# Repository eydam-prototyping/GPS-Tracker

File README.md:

# GPS Tracker Project Documentation

## Project Overview
This project involves developing a GPS tracker using a Raspberry Pi Pico (RP2040) and a SIM7040G module with a built-in GPS. The device will publish its location and cell data to AWS IoT Core every 5 minutes.

## Hardware Components
- **Raspberry Pi Pico (RP2040)**: Main microcontroller.
- **SIM7040G Module**: Provides LTE connectivity and GPS functionality.
- **Battery**: Powers the device.

## Software and Connectivity
- **MicroPython**: Programming language for the Raspberry Pi Pico.
- **AWS IoT Core**: Cloud service for receiving and storing GPS data.

## State Machine Design
### States
1. **Boot State**: System initialization and hardware checks.
2. **Configuration State**: Network and MQTT setup, GPS module initialization.
3. **Idle State**: Low-power mode between data transmissions.
4. **Track State**: Active data retrieval and transmission to AWS.
5. **Error State**: Error detection and handling.

## Error Handling Best Practices
- Clear identification and logging of errors.
- Graceful degradation and automated recovery.
- User notification for critical errors.
- Regular health checks for system components.

## Power Management
Implement power-saving techniques, especially in the Idle State, to extend battery life.

## Future Steps
- Testing and debugging the system.
- Designing a custom PCB integrating all components.
- Optimizing for efficient power usage and network reliability.

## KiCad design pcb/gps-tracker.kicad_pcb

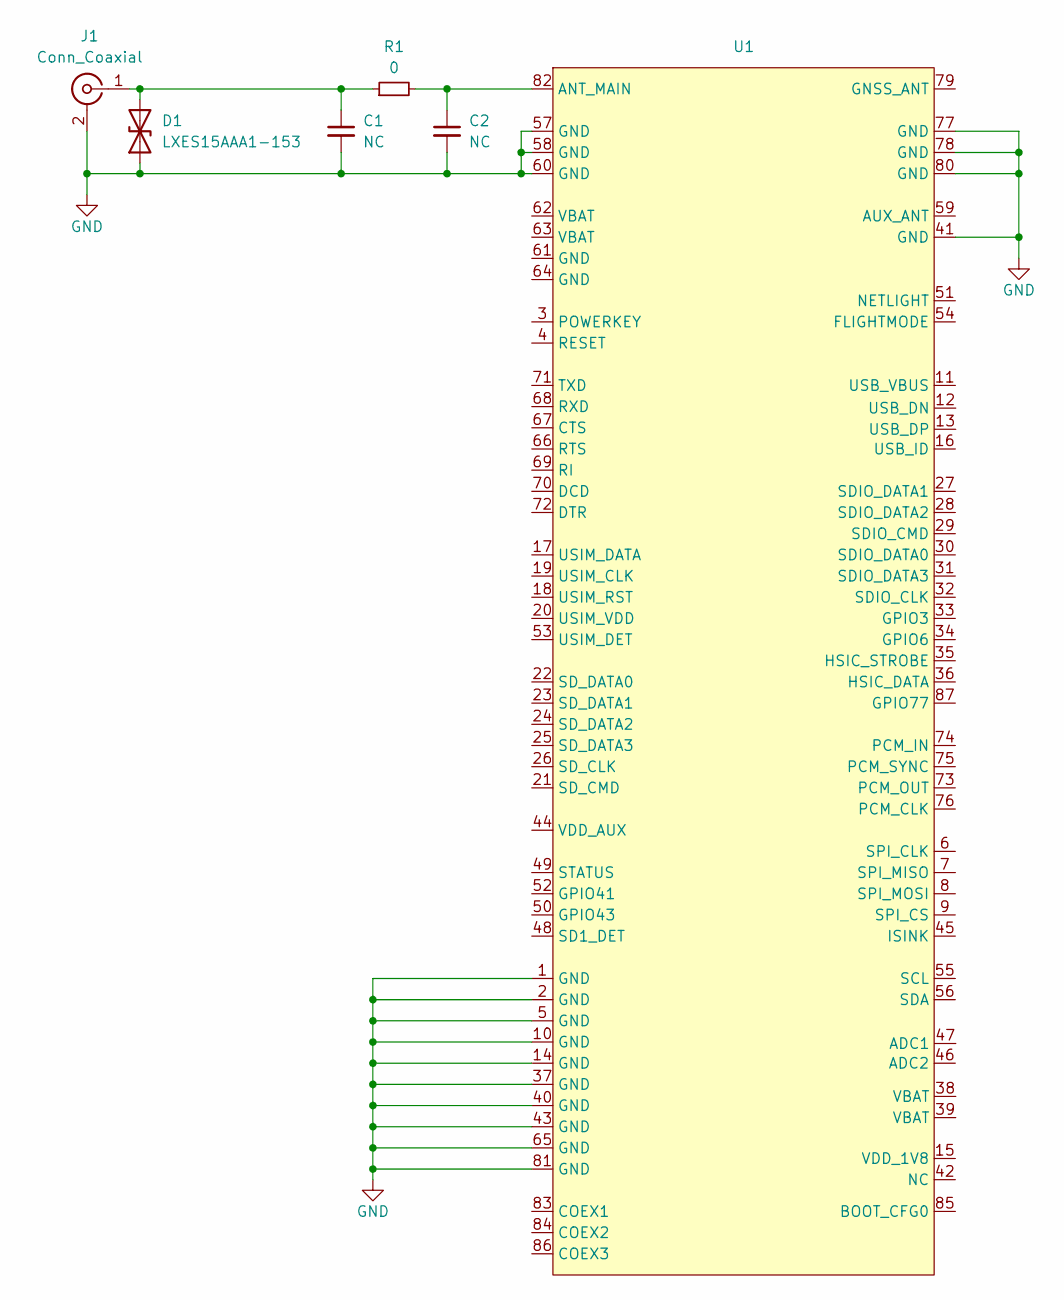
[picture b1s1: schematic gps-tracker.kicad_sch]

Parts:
C1, C2: NC; C_0805_2012Metric_Pad1.18x1.45mm_HandSolder
D1: LXES15AAA1-153; D_0402_1005Metric; JLCPCB C5210978
J1: Conn_Coaxial; SMA_Molex_73251-2120_EdgeMount_Horizontal; JLCPCB C496550
R1: 0; R_0805_2012Metric_Pad1.20x1.40mm_HandSolder
U1: SIMCOM7600E

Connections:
GND: C1.2, C2.2, D1.1 (A1), J1.2 (Ext), U1.1 (GND), U1.2 (GND), U1.5 (GND), U1.10 (GND), U1.14 (GND), U1.37 (GND), U1.40 (GND), U1.41 (GND), U1.43 (GND), U1.57 (GND), U1.58 (GND), U1.60 (GND), U1.65 (GND), U1.77 (GND), U1.78 (GND), U1.80 (GND), U1.81 (GND)
unnamed: C1.1, D1.2 (A2), J1.1 (In), R1.1
unnamed: C2.1, R1.2, U1.82 (ANT_MAIN)

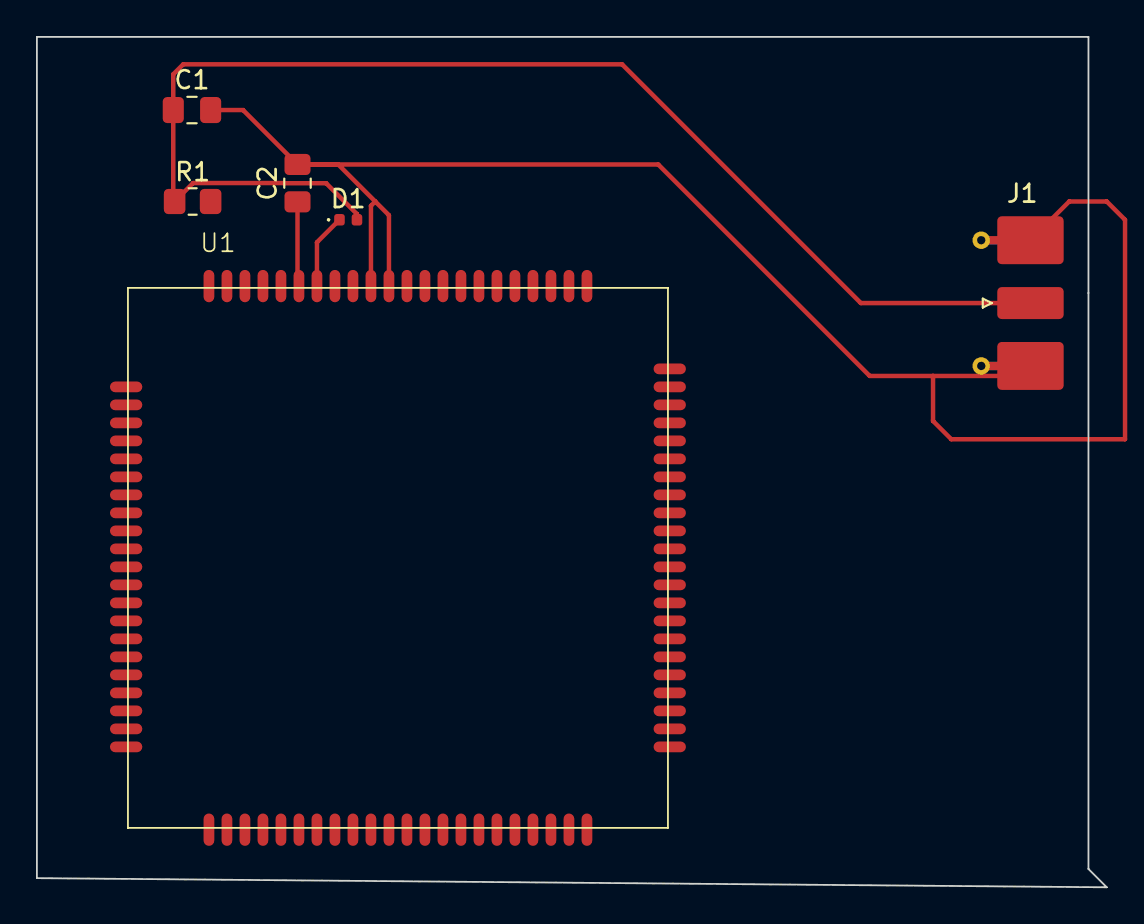
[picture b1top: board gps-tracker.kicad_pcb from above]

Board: 2 copper layers, 59.4 x 47.2 mm, 6 parts (0 on the bottom side), 3 nets.

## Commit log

2024-01-16 slash fixed
2024-02-14 functionality added
2024-02-14 Docstrings added
2024-02-14 Comments
2024-02-14 Docstrings
2024-02-18 pcb added
2024-02-18 workflow added
2024-02-18 kibot
2024-02-18 workflow
2024-02-18 test
